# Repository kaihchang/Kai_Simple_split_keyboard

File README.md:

# Kai Simple, an easy-to-build diodeless, wireless split keyboard

Kai Simple is a cradio (or some call it Sweep) variation that fits author's hands best.
Author's first KB design: https://github.com/kaihchang/Ascend_splay_split_keyboard

👉 ZMK config | [Dongle-less](https://github.com/kaihchang/zmk-config-kai-simple) | [With Dongle](https://github.com/kaihchang/zmk-config-kai-simple-dongle)

MCUs face up for englmaxi's ZMK on-board LED widget. Front-facing built-in LEDs are utilized to present battery and connection status. I use n!n replicas, they only have 1 led each, so sadly no layer change indication.

| Images             |
:-------------------------:
New v4 case available!
|
|
  |
  |
  |

I've been using my last Ascend KB for a month, while it is comfortable, MX switches are still relatively big and wide. Maybe it's bc I have small hands or was used to Sweep before it, I started missing Chocs, so that's why there's this Simple.
I'll probably stick with ZMK but just in case something went wrong with the power circuits (unlikely), I left a pin for TRRS connectors.

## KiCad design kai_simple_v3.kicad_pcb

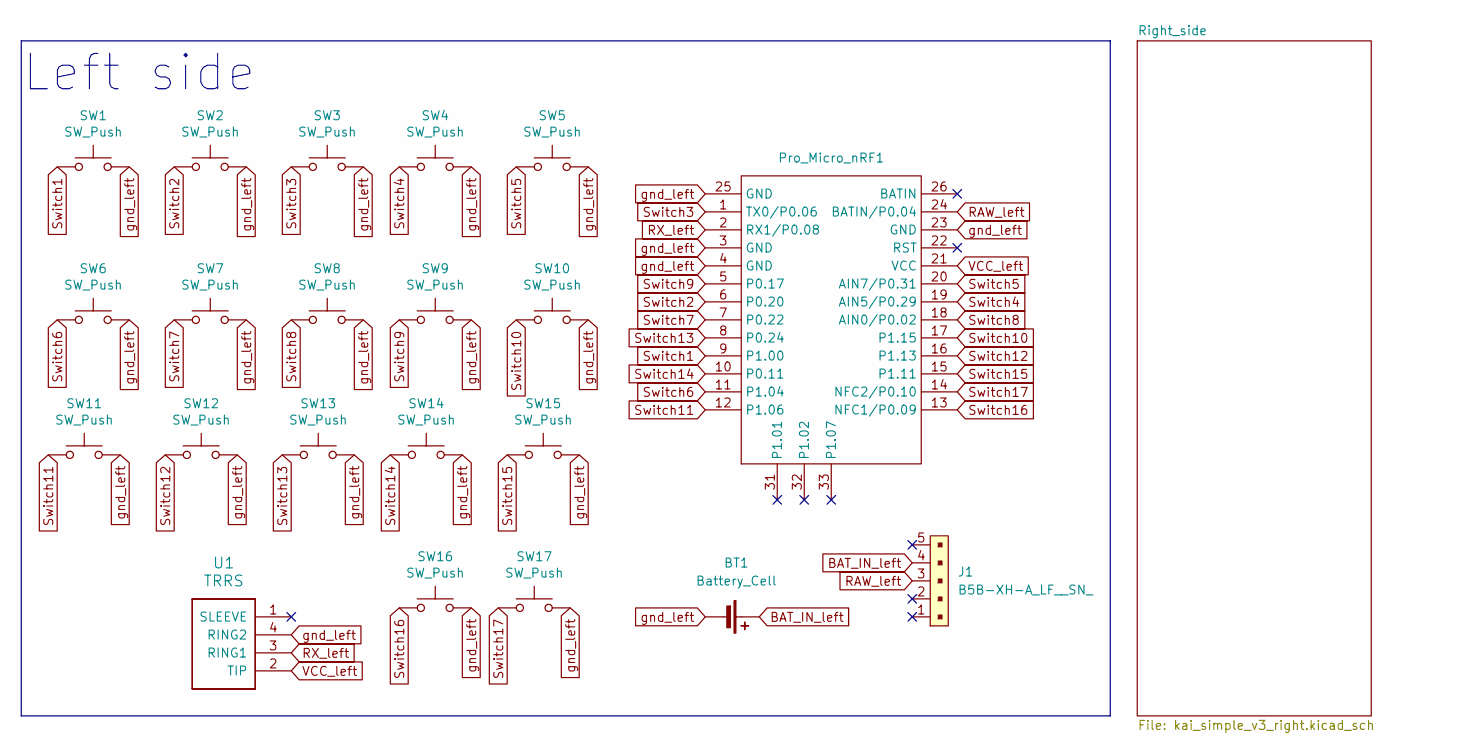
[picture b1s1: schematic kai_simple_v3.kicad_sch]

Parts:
BT1: Battery_Cell; JST_PH_reversible
J1: B5B-XH-A_LF__SN_; Switch_slide_TH_5P; MPN B5B-XH-A(LF)(SN); Digi-Key_PN 455-2270-ND
Pro_Micro_nRF1: Pro Micro nRF52840
SW1, SW2, SW3, SW4, SW5, SW6, SW7, SW8, SW9, SW10, SW11, SW12, SW13, SW14, SW15, SW16, SW17: SW_Push; Choc_v1v2_pretty
U1: TRRS; TRRS_PJ-320A

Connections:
BAT_IN_left: BT1.1 (+), J1.4
RAW_left: J1.3, Pro_Micro_nRF1.24 (BATIN/P0.04)
RX_left: Pro_Micro_nRF1.2 (RX1/P0.08), U1.3 (RING1)
Switch1: Pro_Micro_nRF1.9 (P1.00), SW1.1
Switch2: Pro_Micro_nRF1.6 (P0.20), SW2.1
Switch3: Pro_Micro_nRF1.1 (TX0/P0.06), SW3.1
Switch4: Pro_Micro_nRF1.19 (AIN5/P0.29), SW4.1
Switch5: Pro_Micro_nRF1.20 (AIN7/P0.31), SW5.1
Switch6: Pro_Micro_nRF1.11 (P1.04), SW6.1
Switch7: Pro_Micro_nRF1.7 (P0.22), SW7.1
Switch8: Pro_Micro_nRF1.18 (AIN0/P0.02), SW8.1
Switch9: Pro_Micro_nRF1.5 (P0.17), SW9.1
Switch10: Pro_Micro_nRF1.17 (P1.15), SW10.1
Switch11: Pro_Micro_nRF1.12 (P1.06), SW11.1
Switch12: Pro_Micro_nRF1.16 (P1.13), SW12.1
Switch13: Pro_Micro_nRF1.8 (P0.24), SW13.1
Switch14: Pro_Micro_nRF1.10 (P0.11), SW14.1
Switch15: Pro_Micro_nRF1.15 (P1.11), SW15.1
Switch16: Pro_Micro_nRF1.13 (NFC1/P0.09), SW16.1
Switch17: Pro_Micro_nRF1.14 (NFC2/P0.10), SW17.1
VCC_left: Pro_Micro_nRF1.21 (VCC), U1.2 (TIP)
gnd_left: BT1.2 (-), Pro_Micro_nRF1.3 (GND), Pro_Micro_nRF1.4 (GND), Pro_Micro_nRF1.23 (GND), Pro_Micro_nRF1.25 (GND), SW1.2, SW2.2, SW3.2, SW4.2, SW5.2, SW6.2, SW7.2, SW8.2, SW9.2, SW10.2, SW11.2, SW12.2, SW13.2, SW14.2, SW15.2, SW16.2, SW17.2, U1.4 (RING2)

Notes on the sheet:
Left side

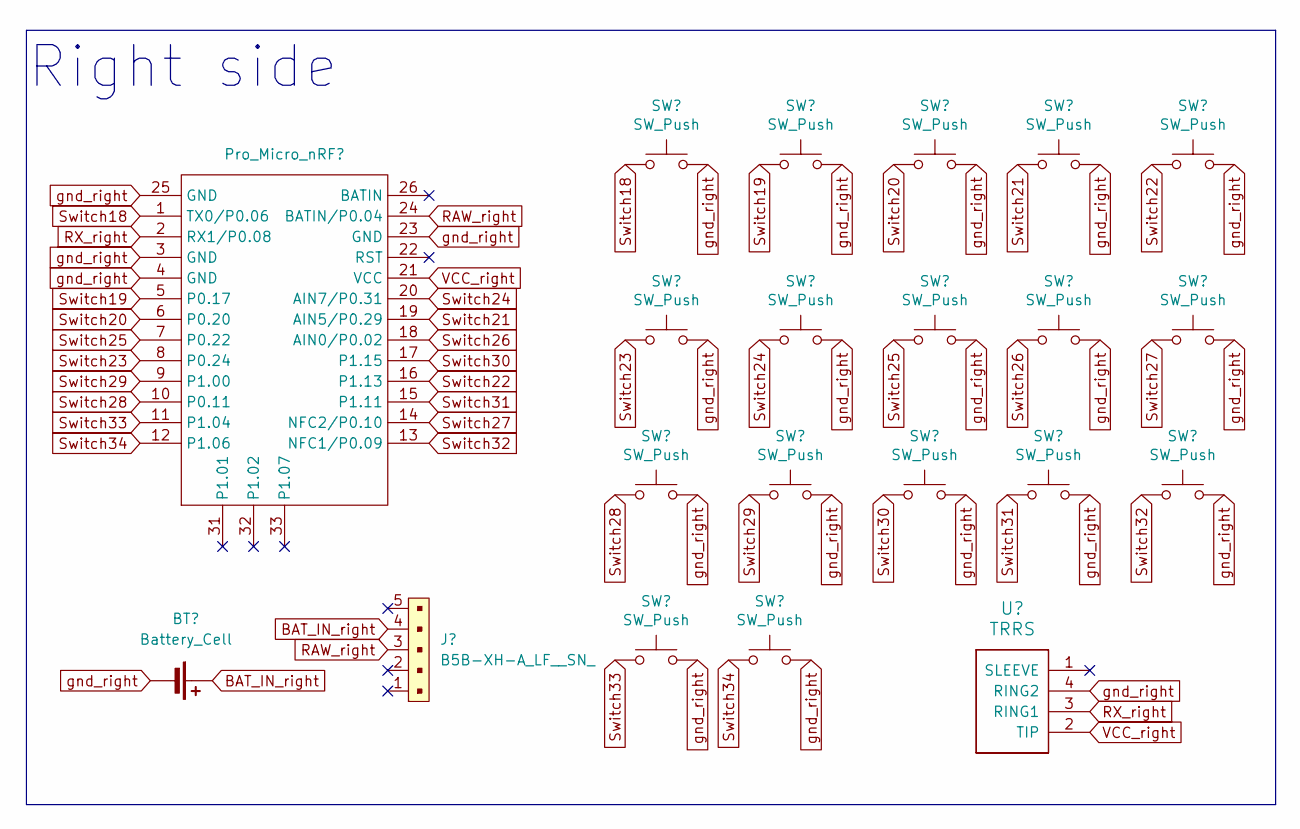
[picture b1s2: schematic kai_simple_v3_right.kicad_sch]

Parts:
BT2: Battery_Cell; JST_PH_reversible
J2: B5B-XH-A_LF__SN_; Switch_slide_TH_5P; MPN B5B-XH-A(LF)(SN); Digi-Key_PN 455-2270-ND
Pro_Micro_nRF2: Pro Micro nRF52840
SW18, SW19, SW20, SW21, SW22, SW23, SW24, SW25, SW26, SW27, SW28, SW29, SW30, SW31, SW32, SW33, SW34: SW_Push; Choc_v1v2_pretty
U2: TRRS; TRRS_PJ-320A

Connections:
BAT_IN_right: BT2.1 (+), J2.4
RAW_right: J2.3, Pro_Micro_nRF2.24 (BATIN/P0.04)
RX_right: Pro_Micro_nRF2.2 (RX1/P0.08), U2.3 (RING1)
Switch18: Pro_Micro_nRF2.1 (TX0/P0.06), SW18.1
Switch19: Pro_Micro_nRF2.5 (P0.17), SW19.1
Switch20: Pro_Micro_nRF2.6 (P0.20), SW20.1
Switch21: Pro_Micro_nRF2.19 (AIN5/P0.29), SW21.1
Switch22: Pro_Micro_nRF2.16 (P1.13), SW22.1
Switch23: Pro_Micro_nRF2.8 (P0.24), SW23.1
Switch24: Pro_Micro_nRF2.20 (AIN7/P0.31), SW24.1
Switch25: Pro_Micro_nRF2.7 (P0.22), SW25.1
Switch26: Pro_Micro_nRF2.18 (AIN0/P0.02), SW26.1
Switch27: Pro_Micro_nRF2.14 (NFC2/P0.10), SW27.1
Switch28: Pro_Micro_nRF2.10 (P0.11), SW28.1
Switch29: Pro_Micro_nRF2.9 (P1.00), SW29.1
Switch30: Pro_Micro_nRF2.17 (P1.15), SW30.1
Switch31: Pro_Micro_nRF2.15 (P1.11), SW31.1
Switch32: Pro_Micro_nRF2.13 (NFC1/P0.09), SW32.1
Switch33: Pro_Micro_nRF2.11 (P1.04), SW33.1
Switch34: Pro_Micro_nRF2.12 (P1.06), SW34.1
VCC_right: Pro_Micro_nRF2.21 (VCC), U2.2 (TIP)
gnd_right: BT2.2 (-), Pro_Micro_nRF2.3 (GND), Pro_Micro_nRF2.4 (GND), Pro_Micro_nRF2.23 (GND), Pro_Micro_nRF2.25 (GND), SW18.2, SW19.2, SW20.2, SW21.2, SW22.2, SW23.2, SW24.2, SW25.2, SW26.2, SW27.2, SW28.2, SW29.2, SW30.2, SW31.2, SW32.2, SW33.2, SW34.2, U2.4 (RING2)

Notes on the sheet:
Right side

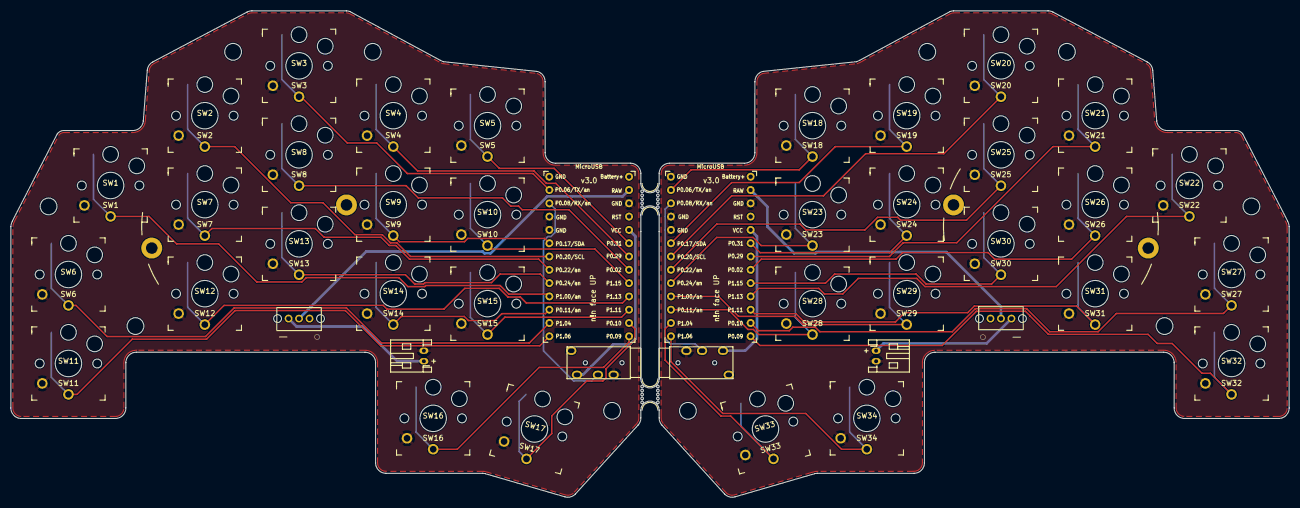
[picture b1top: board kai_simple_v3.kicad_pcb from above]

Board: 2 copper layers, 244.2 x 92.9 mm, 44 parts (0 on the bottom side), 44 nets.

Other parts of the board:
mouse-bite-3mm-slot, mouse-bite-3mm-slot#2: VAL**; mouse-bite-3mm-slot

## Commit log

2024-04-08 migrate to v3
2024-04-17 add step file
2025-10-20 add v2 & v3 case files
2025-10-20 add version 4 with 3mf file
2026-02-20 Update README to include new v4 case details
    Added information about the new v4 case and included an image.
